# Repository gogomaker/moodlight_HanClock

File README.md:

# moodlight_HanClock
와디즈에 펀딩되었던 얘쁜 한글시계 따라 만들기

# 제작동기

참 구글이란 게 신기하다. 내가 한글시계 만들겠다고 온 구글(?)에 설쳐 다니다 보니, 와디즈에서 펀딩 진행했었던 아름다운 시계를 뙇 하고 보여주는 것이 아닌가.

나란 사람. 수학적이지만(?) 갬성 있는 사람.

참지 못하고 구매하려 하였으나 파는 곳이 없어 직접 만들기로 한다...

# 제작일기
2021-02-27: 아름다움에 이끌리어 제작을 시작하였다.

2021-04-14: 그 이후로 바뻐서 작업 못 하다가 다시 시작함

2021-06-15: 컴파일 에러 수정 

2021-06-18: 오늘은 LED관련 제어 함수를 생성하였다. 요즘 따라 작업이 아주 잘 된다.

2021-06-19: 오늘은 LED관련 제어 함수를 모두 완성하였다. 
실제로 실행하였을 때는 제대로 동작하지 않는 부분이 있을 것 같다만, 
논리적으로는 없는 것 같다. 또한, 코드 설명 주석을 수정하였고, LED의 delay 를 제외하고는
모두 다 완성하였다.

2021-06-20: 오늘은 프로그램을 완성하였다. 그리고 PCB설계의 엄청난 에러를 수정하였다.
우선, 프로그램은 기존에 있던 코드를 읽기 좋게 다듬고, 몇가지 변수를 추가하고, 코드를 정돈하였다.
또한, PCB설계에서 LED의 극을 잘못 설정해 놓았었기에, 이 또한 수정하였고,
'시' LED의 (-) 극을 digital pin이 아닌 ground로 바로 연결하였다.(이에 맞게 프로그램도 수정하였다)

2021-06-24: 오늘은 내 옛 노트북을 사용할 수 있게 설정한다고 바뻤다. 
오늘, 옛 노트북에 이 프로젝트를 연동시켜 놓았다.
앞으로는, git push뿐 아니라 git pull도 잘 연습할 수 있을 것 같다.

2021-07-15: 오늘은 시계를 어떻게 만들지, 특히 회로에 대한 부분을 전체적으로 점검했다.

2023-11-20: 오랜만에 (무려 2년만에!) 다시 돌아왔다. 
이제 다시 이 시계를 살려보려 한다. \
아마 디자인을 완전히 갈아엎고 시작할 듯 하다.

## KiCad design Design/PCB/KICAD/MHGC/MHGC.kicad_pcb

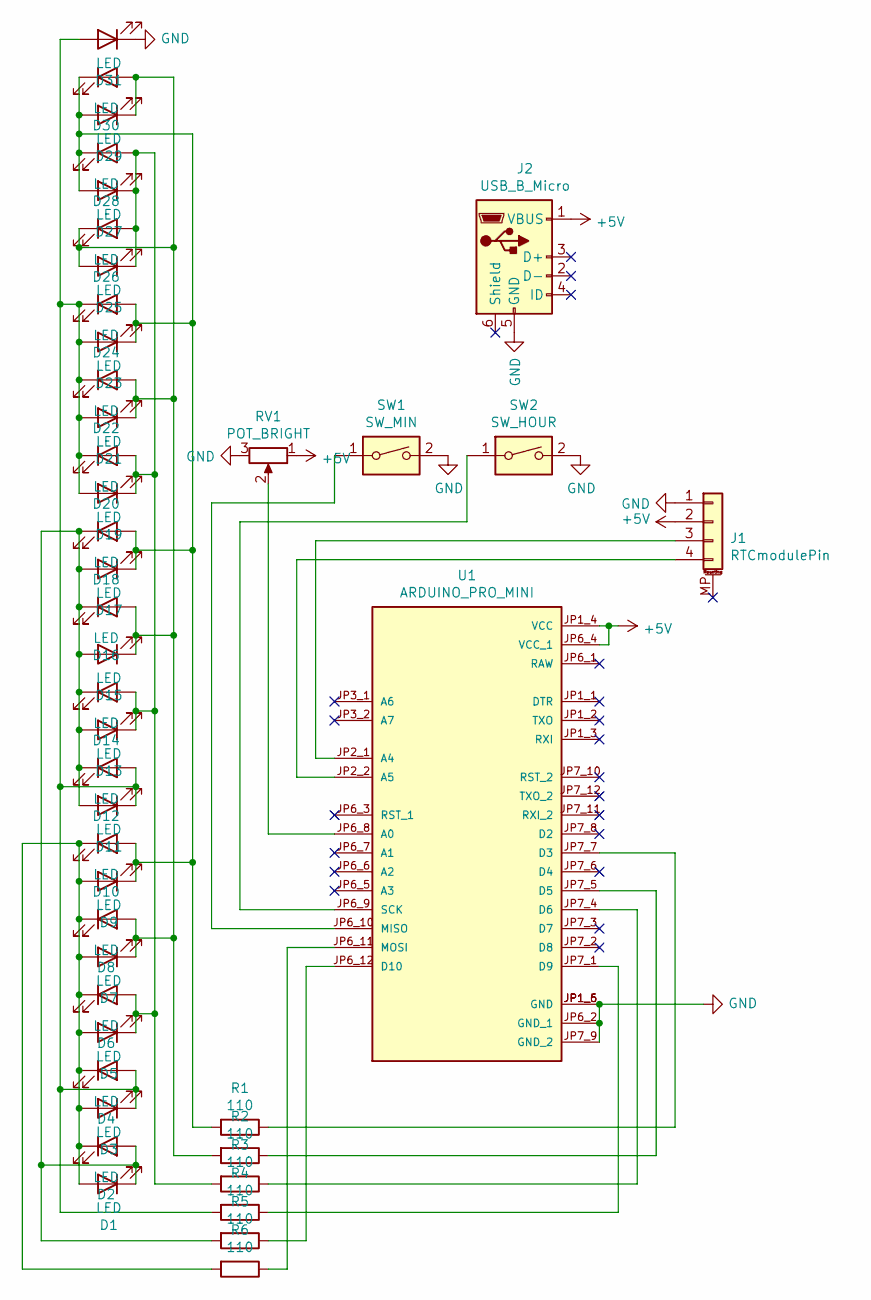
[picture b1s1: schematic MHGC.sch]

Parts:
D1, D2, D3, D4, D5, D6, D7, D8, D9, D10, D11, D12, D13, D14, D15, D16, D17, D18, D19, D20, D21, D22, D23, D24, D25, D26, D27, D28, D29, D30, D31: LED; 3216LED
J1: RTCmodulePin; PinSocket_1x04_P2.54mm_Vertical
J2: USB_B_Micro; USB_Micro-B_Amphenol_10118194_Horizontal
R1, R2, R3, R4, R5, R6: 110; 3216R
RV1: POT_BRIGHT
SW1: SW_MIN; KLT_SW
SW2: SW_HOUR; KLT_SW
U1: ARDUINO_PRO_MINI; MODULE_ARDUINO_PRO_MINI; PARTREV N/A

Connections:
+5V: J1.2, J2.1 (VBUS), RV1.1, U1.JP1_4 (VCC), U1.JP6_4 (VCC_1)
GND: D31.1 (K), J1.1, J2.5 (GND), RV1.3, SW1.2, SW2.2, U1.JP1_5 (GND), U1.JP1_6 (GND), U1.JP6_2 (GND_1), U1.JP7_9 (GND_2)
unnamed: D1.1 (K), D2.2 (A), D11.2 (A), D12.1 (K), D13.2 (A), D14.1 (K), D15.2 (A), D16.1 (K), D17.2 (A), D18.1 (K), R5.2
unnamed: D1.2 (A), D2.1 (K), D3.2 (A), D4.1 (K), D5.2 (A), D6.1 (K), D7.2 (A), D8.1 (K), D9.2 (A), D10.1 (K), R6.2
unnamed: D9.1 (K), D10.2 (A), D17.1 (K), D18.2 (A), D23.1 (K), D24.2 (A), D27.2 (A), D28.1 (K), D29.2 (A), D30.1 (K), R1.2
unnamed: D3.1 (K), D4.2 (A), D11.1 (K), D12.2 (A), D19.2 (A), D20.1 (K), D21.2 (A), D22.1 (K), D23.2 (A), D24.1 (K), D31.2 (A), R4.2
unnamed: D5.1 (K), D6.2 (A), D13.1 (K), D14.2 (A), D19.1 (K), D20.2 (A), D25.1 (K), D26.2 (A), D27.1 (K), D28.2 (A), R3.2
unnamed: D7.1 (K), D8.2 (A), D15.1 (K), D16.2 (A), D21.1 (K), D22.2 (A), D25.2 (A), D26.1 (K), D29.1 (K), D30.2 (A), R2.2
unnamed: J1.3, U1.JP2_1 (A4)
unnamed: J1.4, U1.JP2_2 (A5)
unnamed: R1.1, U1.JP7_7 (D3)
unnamed: R2.1, U1.JP7_5 (D5)
unnamed: R3.1, U1.JP7_4 (D6)
unnamed: R4.1, U1.JP7_1 (D9)
unnamed: R5.1, U1.JP6_12 (D10)
unnamed: R6.1, U1.JP6_11 (MOSI)
unnamed: RV1.2, U1.JP6_8 (A0)
unnamed: SW1.1, U1.JP6_10 (MISO)
unnamed: SW2.1, U1.JP6_9 (SCK)

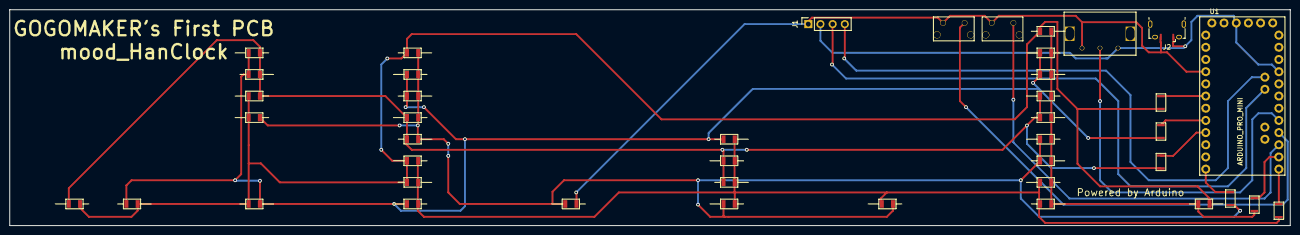
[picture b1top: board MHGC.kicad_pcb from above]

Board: 2 copper layers, 267.0 x 45.0 mm, 43 parts (0 on the bottom side), 19 nets.

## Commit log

2021-06-14 Headerfile complited 헤더파일을 완성하였고, 일단 보이는 모든 에러를 잡았다.
2021-06-15 Solve comfile error 전 커밋에서는 구문 오류는 없었지만 스케치를 컴파일하면 자꾸 에러가 났었다. 해당 문제의 원인이 c_cpp_properties.json이라는 것을 알고 수정하여서 오류를 해결하였다.
2021-06-15 Make button function 버튼 함수를 만들 수 있게 코드 정리하고, 사용하지 않는 변수를 정리하였으며, main루프의 기본 코드도 삽입하였다
2021-06-16 complete button function
2021-06-18 LED control function created LED를 제어하는 함수를 만들었다. displayTime라는 함수를 호출하면, 해당 함수가 turnOnLED함수를 실행시켜서 켜려는 LED핀의 상태를 LED가 켤 수 있게 되도록 한다. 다만, 아직 미흡한 부분이 있어 추가적 보수가 많이 필요하다.
2021-06-18 retouch readme file
2021-06-19 Almost make LED control function LED제어 함수를 거의 다 만들었다. 그러나, 제대로 작동하는지에 대한 의문점이 있고, delay코드는 delayMicroseconds로 바꾸거나 millis를 활용하는 코드로 변경해야 한다. 조만간 이 코드를 시뮬레이션 해 보아야 겠다.
2021-06-20 Complete programming 프로그램의 에러도 다 잡고, 기능도 다 구현했다. 내가 코드만 보기에는 전혀 문제가 없어 보인다. 이제 남은 것은 PCB에 부품들을 조립하여 하드웨어에 이 코드를 업로드 후 테스트 하는 것 뿐... 부디 내가 만든 코드가 문제가 없는 것이길 바란다.
2021-06-24 Sync this project on the second laptop
2021-07-17 Restarted PCB design 오늘 나는 PCB작업프로그램을 OrCAD에서 KiCAD로 바꿨다
2021-07-19 Started PCB design 드디어 PCB에 부품 배치를 시작했다
2021-07-22 Completed PCB design
2021-07-29 Change design files 디자인 파일 중에서, PCB설계에 맞추어 버튼 및 기타 부품이 배치될 공간을 작업하고, 아크릴 관련 공차 설정도 다시 하였다.
2023-11-20 Project-Restart 프로젝트 재정비하고, 다시 시작하기 위한 깃 세팅을 하였다.
